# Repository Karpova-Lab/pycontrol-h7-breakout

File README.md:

> !!! WARNING !!! This is a work in progress. Please see the [discussion](https://github.com/orgs/pyControl/discussions/171) to see updates and provide feedback.
# pyControl H7 Breakout
A pyControl breakout board using an [STM32H743VIT6](https://www.digikey.com/short/7n8h83wr) microcontroller.

- 480 MHz Cortex-M7, 800 KB SRAM, 32 MB QSPI flash
- 10 pyControl RJ45 behavior ports
- 8 position [terminal block](https://www.digikey.com/short/fpqf2rj0) that pairs with a [screw terminal plug](https://www.digikey.com/short/n57m4m7h)
- 2 BNC connectors
- 1 [QWIIC](https://www.sparkfun.com/qwiic) / [Stemma-QT](https://learn.adafruit.com/introducing-adafruit-stemma-qt/what-is-stemma-qt) / [Modulino](https://store.arduino.cc/collections/modulino) connector
- USB type C connector with ESD protection
- On/off toggle switch, 4 user buttons, reset button, and a DFU button for bootloader access
- Power and USB indicator LEDs, 4 user controllable LEDs (red, yellow, green and blue)
- Metal enclosure 
- Mounting hole spacing compatible with [DIN adapters](https://www.digikey.com/short/h7977mfv) that securely mount onto [DIN rail](https://www.digikey.com/en/products/filter/hardware-fasteners-accessories/580?s=N4IgjCBcpgHAzFUBjKAzAhgGwM4FMAaEAeygG0QAWMeWSgThAF0iAHAFyhAGV2AnAJYA7AOYgAvkQC0AJiQhUkfgFdCJciACszcZJBzIFACIBJAHIACPhgFYQRU5eu2dQA)

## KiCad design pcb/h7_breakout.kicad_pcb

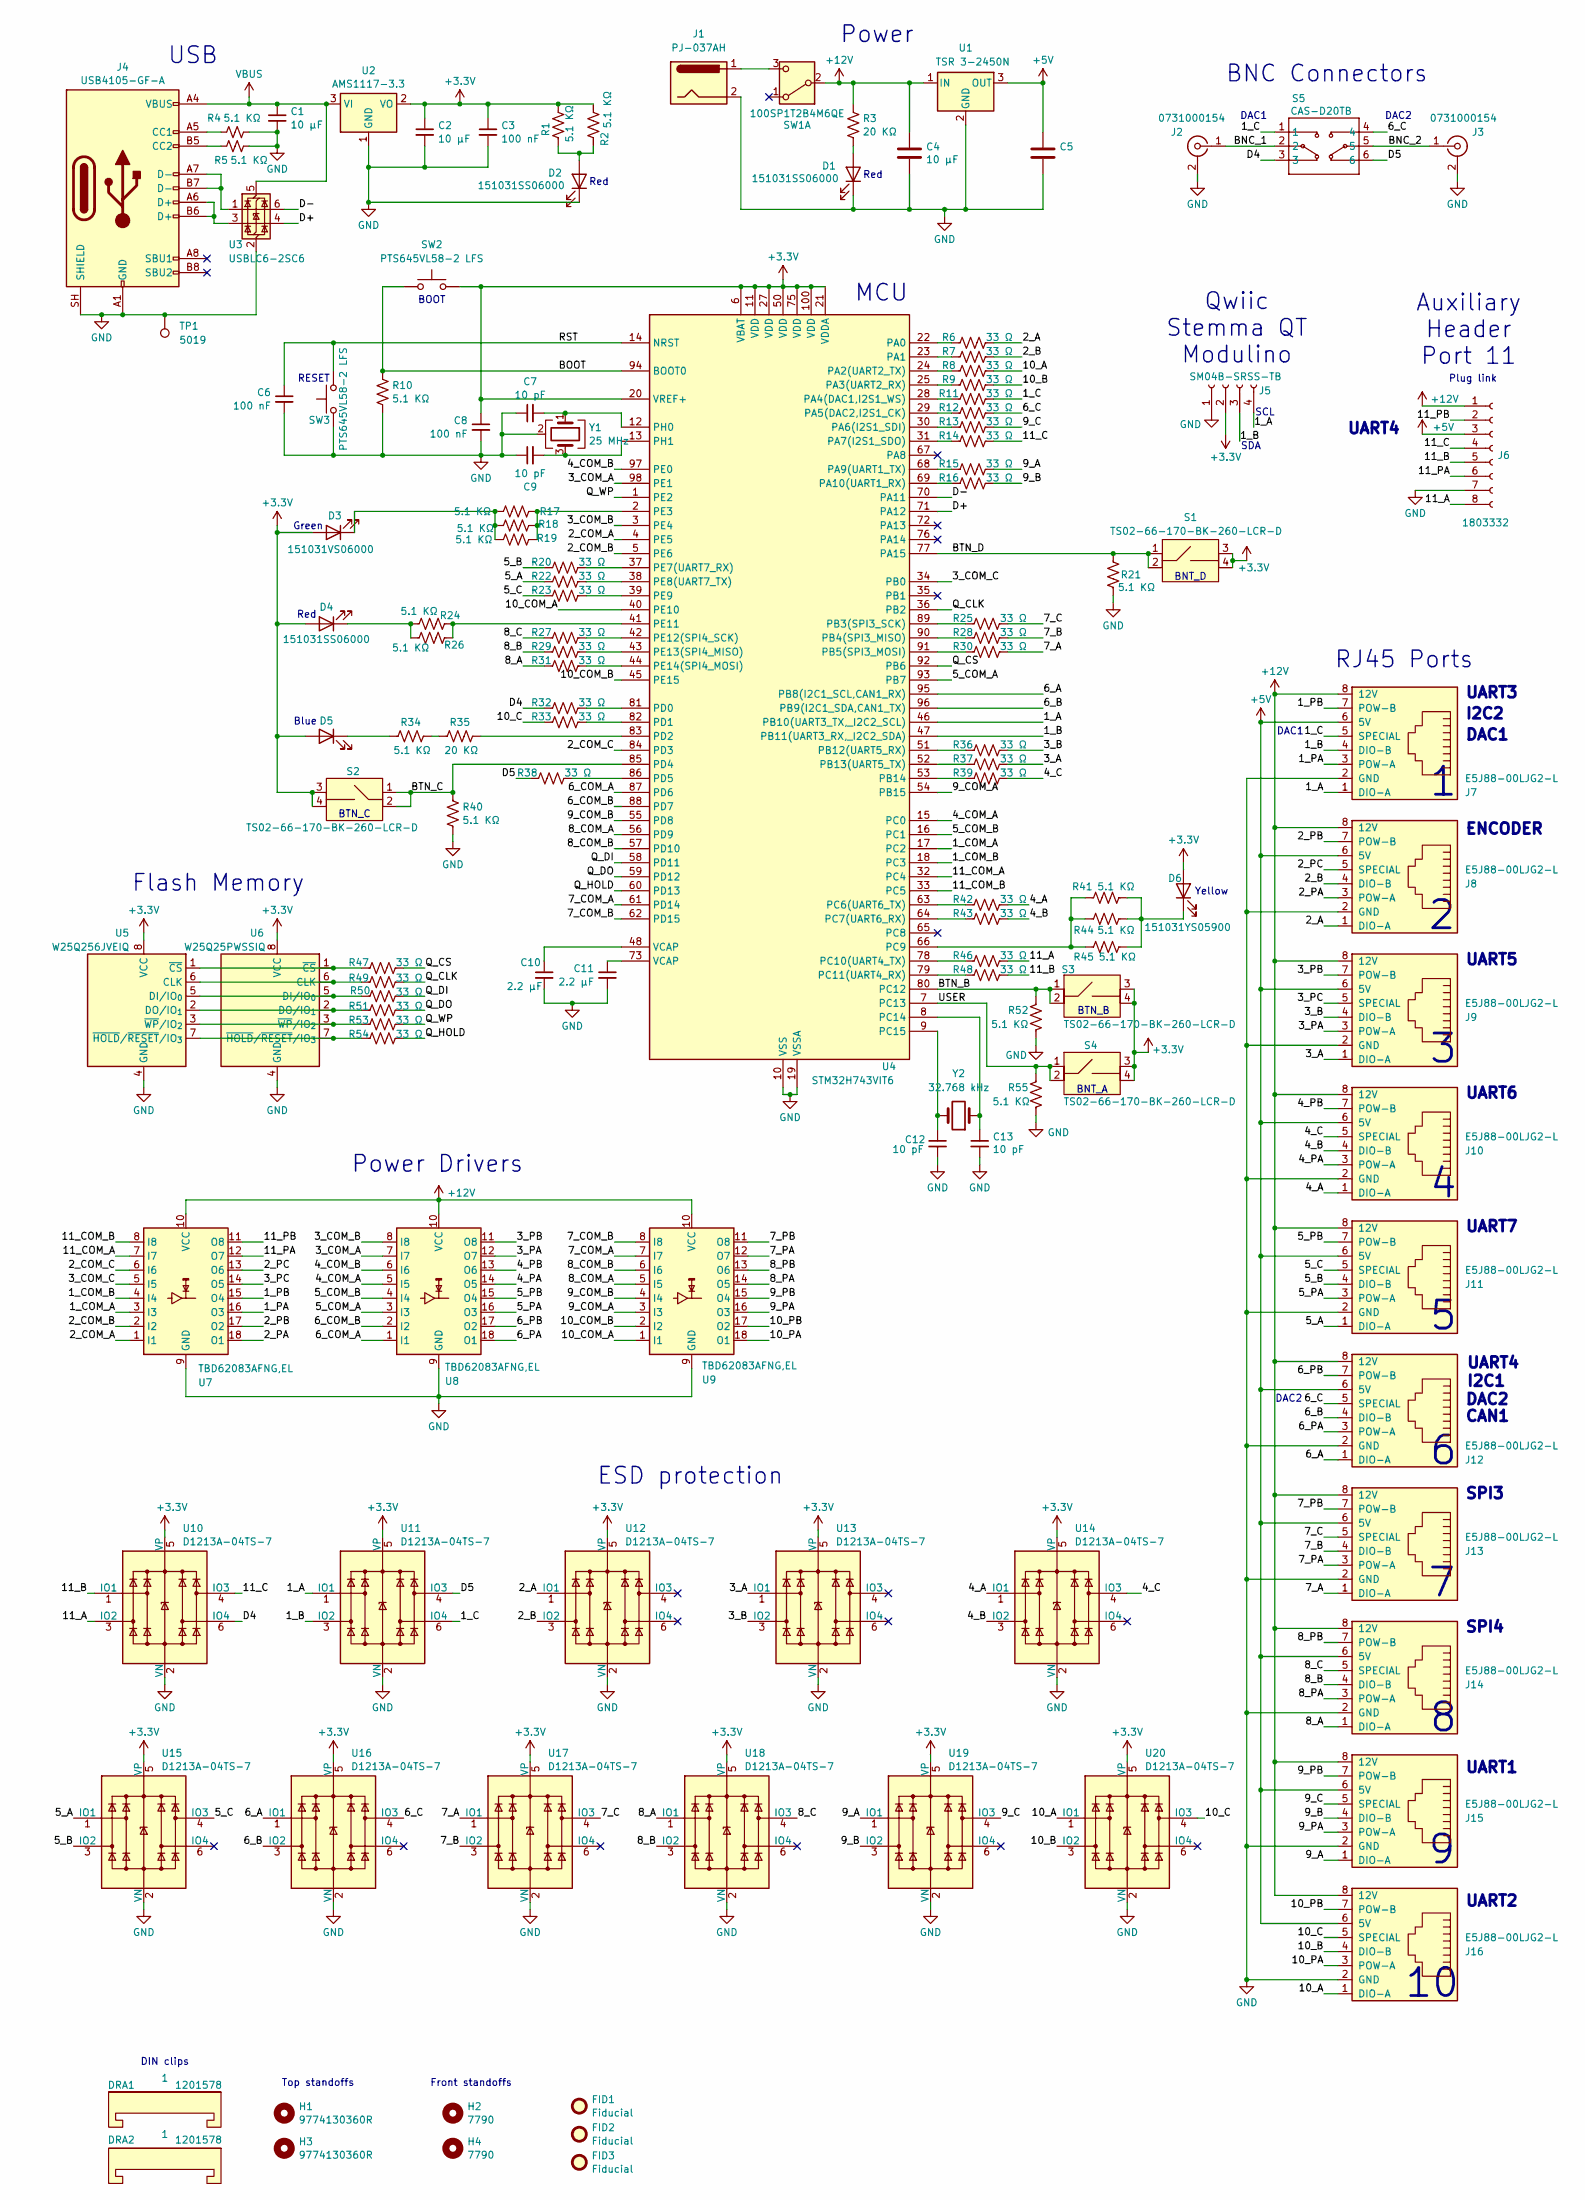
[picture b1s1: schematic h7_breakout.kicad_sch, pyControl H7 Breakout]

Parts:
C1, C2, C4, C5: 10 µF; C_1206_3216Metric_Pad1.33x1.80mm_HandSolder
C3, C6, C8: 100 nF; C_0603_1608Metric_Pad1.08x0.95mm_HandSolder
C7, C9, C12, C13: 10 pF; C_0603_1608Metric_Pad1.08x0.95mm_HandSolder
C10, C11: 2.2 µF; C_0603_1608Metric_Pad1.08x0.95mm_HandSolder
D1, D2, D4: 151031SS06000; LED_D3.0mm
D3: 151031VS06000; LED_D3.0mm
D5: 151033BS03000; LED_D3.0mm
D6: 151031YS05900; LED_D3.0mm
DRA1, DRA2: 1201578; DIN_Clip
FID1, FID2, FID3: Fiducial; Fiducial_0.75mm_Mask2.25mm
H1, H3: 9774130360R; standoff_nut
H2, H4: 7790; RA_screw_mount
J1: PJ-037AH; DC_Jack
J2, J3: 0731000154; BNC RA Jack
J4: USB4105-GF-A; USB_C_Receptacle_GCT_USB4105-xx-A_16P_TopMnt_Horizontal
J5: SM04B-SRSS-TB; JST_SH_SM04B-SRSS-TB_1x04-1MP_P1.00mm_Horizontal
J6: 1803332; PhoenixContact_MC_1,5_8-G-3.81_1x08_P3.81mm_Horizontal
J7, J8, J9, J10, J11, J12, J13, J14, J15, J16: E5J88-00LJG2-L; RJ45_THP_tab_on_top
R1, R2, R4, R5, R10, R17, R18, R19, R21, R24, R26, R34, R40, R41, R44, R45, R52, R55: 5.1 KΩ; R_0603_1608Metric_Pad0.98x0.95mm_HandSolder
R3, R35: 20 KΩ; R_0603_1608Metric_Pad0.98x0.95mm_HandSolder
R6, R7, R8, R9, R11, R12, R13, R14, R15, R16, R20, R22, R23, R25, R27, R28, R29, R30, R31, R32, R33, R36, R37, R38, R39, R42, R43, R46, R47, R48, R49, R50, R51, R53, R54: 33 Ω; R_0603_1608Metric_Pad0.98x0.95mm_HandSolder
S1, S2, S3, S4: TS02-66-170-BK-260-LCR-D; SW_TH_Tactile_TS02-66-170
S5: CAS-D20TB
SW1: 100SP1T2B4M6QE; RA toggle
SW2, SW3: PTS645VL58-2 LFS; SW_Tactile_SPST_Angled_PTS645Vx58-2LFS
TP1: 5019; TestPoint_Plated_Hole_D2.0mm
U1: TSR 3-2450N; Converter_DCDC_traco_3A
U2: AMS1117-3.3; SOT-223-3_TabPin2
U3: USBLC6-2SC6; SOT-23-6; LCSC C7519
U4: STM32H743VIT6; LQFP-100_14x14mm_P0.5mm; LCSC C114409
U5: W25Q256JVEIQ; WSON-8-1EP_8x6mm_P1.27mm_EP3.4x4.3mm; LCSC C97522
U6: W25Q25PWSSIQ; SOIC-8_5.3x5.3mm_P1.27mm
U7, U8, U9: TBD62083AFNG,EL; SSOP-18_4.4x6.5mm_P0.65mm; LCSC C163229
U10, U11, U12, U13, U14, U15, U16, U17, U18, U19, U20: D1213A-04TS-7; SOT-23-6; LCSC C460588
Y1: 25 MHz; crystal_STDCRS2-25M
Y2: 32.768 kHz; Crystal_SMD_EuroQuartz_EQ161-2Pin_3.2x1.5mm_HandSoldering

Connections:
+5V: C5.1, J6.3, J7.6 (5V), J8.6 (5V), J9.6 (5V), J10.6 (5V), J11.6 (5V), J12.6 (5V), J13.6 (5V), J14.6 (5V), J15.6 (5V), J16.6 (5V), U1.3 (OUT)
+12V: C4.1, J6.1, J7.8 (12V), J8.8 (12V), J9.8 (12V), J10.8 (12V), J11.8 (12V), J12.8 (12V), J13.8 (12V), J14.8 (12V), J15.8 (12V), J16.8 (12V), R3.1, SW1.2 (B), U1.1 (IN), U7.10 (VCC), U8.10 (VCC), U9.10 (VCC)
/1_A: J5.4, J7.1 (DIO-A), U4.46 (PB10(UART3_TX,_I2C2_SCL)), U11.1 (IO1)
/1_B: J5.3, J7.4 (DIO-B), U4.47 (PB11(UART3_RX,_I2C2_SDA)), U11.3 (IO2)
/1_C: J7.5 (SPECIAL), R11.2, S5.1, U11.6 (IO4)
/1_COM_A: U4.17 (PC2), U7.3 (I3)
/1_COM_B: U4.18 (PC3), U7.4 (I4)
/1_PA: J7.3 (POW-A), U7.16 (O3)
/1_PB: J7.7 (POW-B), U7.15 (O4)
/2_A: J8.1 (DIO-A), R6.2, U12.1 (IO1)
/2_B: J8.4 (DIO-B), R7.2, U12.3 (IO2)
/2_COM_A: U4.4 (PE5), U7.1 (I1)
/2_COM_B: U4.5 (PE6), U7.2 (I2)
/2_COM_C: U4.84 (PD3), U7.6 (I6)
/2_PA: J8.3 (POW-A), U7.18 (O1)
/2_PB: J8.7 (POW-B), U7.17 (O2)
/2_PC: J8.5 (SPECIAL), U7.13 (O6)
/3_A: J9.1 (DIO-A), R37.2, U13.1 (IO1)
/3_B: J9.4 (DIO-B), R36.2, U13.3 (IO2)
/3_COM_A: U4.98 (PE1), U8.7 (I7)
/3_COM_B: U4.3 (PE4), U8.8 (I8)
/3_COM_C: U4.34 (PB0), U7.5 (I5)
/3_PA: J9.3 (POW-A), U8.12 (O7)
/3_PB: J9.7 (POW-B), U8.11 (O8)
/3_PC: J9.5 (SPECIAL), U7.14 (O5)
/4_A: J10.1 (DIO-A), R42.2, U14.1 (IO1)
/4_B: J10.4 (DIO-B), R43.2, U14.3 (IO2)
/4_C: J10.5 (SPECIAL), R39.2, U14.4 (IO3)
/4_COM_A: U4.15 (PC0), U8.5 (I5)
/4_COM_B: U4.97 (PE0), U8.6 (I6)
/4_PA: J10.3 (POW-A), U8.14 (O5)
/4_PB: J10.7 (POW-B), U8.13 (O6)
/5_A: J11.1 (DIO-A), R22.1, U15.1 (IO1)
/5_B: J11.4 (DIO-B), R20.1, U15.3 (IO2)
/5_C: J11.5 (SPECIAL), R23.1, U15.4 (IO3)
/5_COM_A: U4.93 (PB7), U8.3 (I3)
/5_COM_B: U4.16 (PC1), U8.4 (I4)
/5_PA: J11.3 (POW-A), U8.16 (O3)
/5_PB: J11.7 (POW-B), U8.15 (O4)
/6_A: J12.1 (DIO-A), U4.95 (PB8(I2C1_SCL,CAN1_RX)), U16.1 (IO1)
/6_B: J12.4 (DIO-B), U4.96 (PB9(I2C1_SDA,CAN1_TX)), U16.3 (IO2)
/6_C: J12.5 (SPECIAL), R12.2, S5.4, U16.4 (IO3)
/6_COM_A: U4.87 (PD6), U8.1 (I1)
/6_COM_B: U4.88 (PD7), U8.2 (I2)
/6_PA: J12.3 (POW-A), U8.18 (O1)
/6_PB: J12.7 (POW-B), U8.17 (O2)
/7_A: J13.1 (DIO-A), R30.2, U17.1 (IO1)
/7_B: J13.4 (DIO-B), R28.2, U17.3 (IO2)
/7_C: J13.5 (SPECIAL), R25.2, U17.4 (IO3)
/7_COM_A: U4.61 (PD14), U9.7 (I7)
/7_COM_B: U4.62 (PD15), U9.8 (I8)
/7_PA: J13.3 (POW-A), U9.12 (O7)
/7_PB: J13.7 (POW-B), U9.11 (O8)
/8_A: J14.1 (DIO-A), R31.1, U18.1 (IO1)
/8_B: J14.4 (DIO-B), R29.1, U18.3 (IO2)
/8_C: J14.5 (SPECIAL), R27.1, U18.4 (IO3)
/8_COM_A: U4.56 (PD9), U9.5 (I5)
/8_COM_B: U4.57 (PD10), U9.6 (I6)
/8_PA: J14.3 (POW-A), U9.14 (O5)
/8_PB: J14.7 (POW-B), U9.13 (O6)
/9_A: J15.1 (DIO-A), R15.2, U19.1 (IO1)
/9_B: J15.4 (DIO-B), R16.2, U19.3 (IO2)
/9_C: J15.5 (SPECIAL), R13.2, U19.4 (IO3)
/9_COM_A: U4.54 (PB15), U9.3 (I3)
/9_COM_B: U4.55 (PD8), U9.4 (I4)
/9_PA: J15.3 (POW-A), U9.16 (O3)
/9_PB: J15.7 (POW-B), U9.15 (O4)
/10_A: J16.1 (DIO-A), R8.2, U20.1 (IO1)
/10_B: J16.4 (DIO-B), R9.2, U20.3 (IO2)
/10_C: J16.5 (SPECIAL), R33.1, U20.4 (IO3)
/10_COM_A: U4.40 (PE10), U9.1 (I1)
/10_COM_B: U4.45 (PE15), U9.2 (I2)
/10_PA: J16.3 (POW-A), U9.18 (O1)
/10_PB: J16.7 (POW-B), U9.17 (O2)
/11_A: J6.8, R46.2, U10.3 (IO2)
/11_B: J6.5, R48.2, U10.1 (IO1)
/11_C: J6.4, R14.2, U10.4 (IO3)
/11_COM_A: U4.32 (PC4), U7.7 (I7)
/11_COM_B: U4.33 (PC5), U7.8 (I8)
/11_PA: J6.6, U7.12 (O7)
/11_PB: J6.2, U7.11 (O8)
/BNC_1: J2.1 (In), S5.2
/BNC_2: J3.1 (In), S5.5
/BTN_B: R52.2, S3.1 (in1), S3.2 (in2), U4.80 (PC12)
/BTN_C: R40.2, S2.1 (in1), S2.2 (in2), U4.85 (PD4)
/BTN_D: R21.2, S1.1 (in1), S1.2 (in2), U4.77 (PA15)
/D4: R32.1, S5.3, U10.6 (IO4)
/D5: R38.1, S5.6, U11.4 (IO3)
/D+: U3.4 (I/O2), U4.71 (PA12)
/D-: U3.6 (I/O1), U4.70 (PA11)
/Q_CLK: R49.2, U4.36 (PB2)
/Q_CS: R47.2, U4.92 (PB6)
/Q_DI: R50.2, U4.58 (PD11)
/Q_DO: R51.2, U4.59 (PD12)
/Q_HOLD: R54.2, U4.60 (PD13)
/Q_WP: R53.2, U4.1 (PE2)
/USER: R55.2, S4.1 (in1), S4.2 (in2), U4.7 (PC13)
unnamed: C10.1, U4.48 (VCAP)
unnamed: C11.1, U4.73 (VCAP)
unnamed: D1.2 (A), R3.2
unnamed: D2.2 (A), R1.2, R2.2
unnamed: D3.1 (K), R17.1, R18.1, R19.1
unnamed: D4.1 (K), R24.1, R26.1
unnamed: D5.1 (K), R34.1
unnamed: D6.1 (K), R41.2, R44.2, R45.2
unnamed: J4.A5 (CC1), R4.1
unnamed: J4.B5 (CC2), R5.2
unnamed: J4.A6 (D+), J4.B6 (D+), U3.3 (I/O2)
unnamed: J4.A7 (D-), J4.B7 (D-), U3.1 (I/O1)
unnamed: R34.2, R35.1
unnamed: J1.1, SW1.3 (C)
unnamed: R6.1, U4.22 (PA0)
unnamed: R7.1, U4.23 (PA1)
unnamed: R8.1, U4.24 (PA2(UART2_TX))
unnamed: R9.1, U4.25 (PA3(UART2_RX))
unnamed: R11.1, U4.28 (PA4(DAC1,I2S1_WS))
unnamed: R12.1, U4.29 (PA5(DAC2,I2S1_CK))
unnamed: R13.1, U4.30 (PA6(I2S1_SDI))
unnamed: R14.1, U4.31 (PA7(I2S1_SDO))
unnamed: R15.1, U4.68 (PA9(UART1_TX))
unnamed: R16.1, U4.69 (PA10(UART1_RX))
unnamed: R25.1, U4.89 (PB3(SPI3_SCK))
unnamed: R28.1, U4.90 (PB4(SPI3_MISO))
unnamed: R30.1, U4.91 (PB5(SPI3_MOSI))
unnamed: R36.1, U4.51 (PB12(UART5_RX))
unnamed: R37.1, U4.52 (PB13(UART5_TX))
unnamed: R39.1, U4.53 (PB14)
unnamed: R42.1, U4.63 (PC6(UART6_TX))
unnamed: R43.1, U4.64 (PC7(UART6_RX))
unnamed: R41.1, R44.1, R45.1, U4.66 (PC9)
unnamed: R46.1, U4.78 (PC10(UART4_TX))
unnamed: R48.1, U4.79 (PC11(UART4_RX))
unnamed: C13.1, U4.8 (PC14), Y2.1
unnamed: C12.1, U4.9 (PC15), Y2.2
unnamed: R32.2, U4.81 (PD0)
unnamed: R33.2, U4.82 (PD1)
unnamed: R35.2, U4.83 (PD2)
unnamed: R38.2, U4.86 (PD5)
unnamed: R17.2, R18.2, R19.2, U4.2 (PE3)
unnamed: R20.2, U4.37 (PE7(UART7_RX))
unnamed: R22.2, U4.38 (PE8(UART7_TX))
unnamed: R23.2, U4.39 (PE9)
unnamed: R24.2, R26.2, U4.41 (PE11)
unnamed: R27.2, U4.42 (PE12(SPI4_SCK))
unnamed: R29.2, U4.43 (PE13(SPI4_MISO))
unnamed: R31.2, U4.44 (PE14(SPI4_MOSI))
unnamed: C7.2, U4.12 (PH0), Y1.1
unnamed: C9.2, U4.13 (PH1), Y1.3
unnamed: R49.1, U5.6 (CLK), U6.6 (CLK)
unnamed: R50.1, U5.5 (DI/IO_{0}), U6.5 (DI/IO_{0})
unnamed: R51.1, U5.2 (DO/IO_{1}), U6.2 (DO/IO_{1})
unnamed: R47.1, U5.1 (~CS), U6.1 (~CS)
unnamed: R54.1, U5.7 (~HOLD/~RESET/IO_{3}), U6.7 (~HOLD/~RESET/IO_{3})
unnamed: R53.1, U5.3 (~WP/IO_{2}), U6.3 (~WP/IO_{2})
VBUS: C1.1, J4.A4 (VBUS), J4.A9 (VBUS), J4.B4 (VBUS), J4.B9 (VBUS), U2.3 (VI), U3.5 (VBUS)

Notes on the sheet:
SDA
DAC2
I2C2
UART4
Plug link
Power Drivers
Auxiliary Header Port 11
ESD protection
DIN clips
ENCODER
BOOT
USB
Red
SPI4
Qwiic Stemma QT Modulino
I2C1
BTN_B
RJ45 Ports
BNT_D
SCL
Flash Memory
BNT_A
DAC1
UART6
SPI3
UART1
UART3
Blue
UART7
UART2
RESET
Green
Front standoffs
BNC Connectors
UART5
Power
Yellow
CAN1
BTN_C
MCU

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
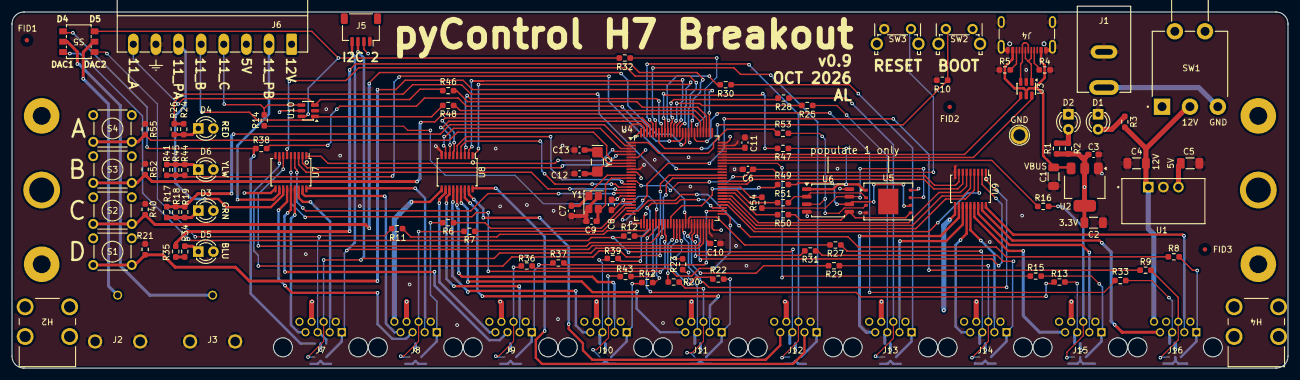
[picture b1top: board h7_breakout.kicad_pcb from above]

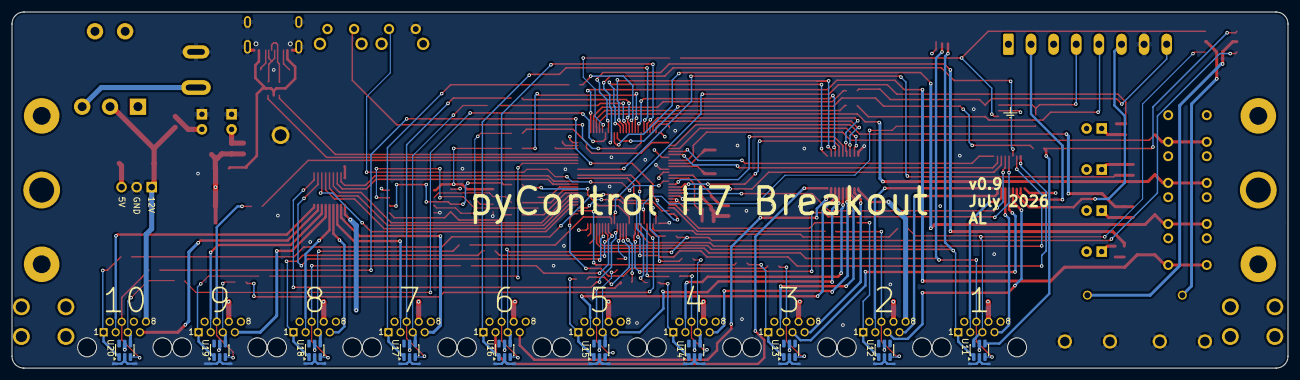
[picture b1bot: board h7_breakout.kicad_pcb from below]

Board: 4 copper layers, 215.0 x 60.0 mm, 130 parts (12 on the bottom side), 159 nets.

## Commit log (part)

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2026-02-25 v0.1
2026-03-12 PCB v0.2
2026-03-25 add Janelia licenses
2026-03-26 PCB v0.3
    don't short the power supply with the on/off switch 🤦
    flipped UART4 pins. TX(4_A)/RX(4_B) was PC11(79)/PC10(78), now PC10(78)/PC11(79)
    connect Vref to 3.3V so DAC works
    change RGB LEDs to 10k
2026-03-26 add readme
2026-03-26 readme update
2026-04-16 PCB v0.4
    - was 2 layer, now 4 layer board
    - was USB type B, now USB type C connector
    - was SMA coaxial connectors, now BNC
    - was 12 ports, now 10 ports
    - added POW_C pins to 2 of the ports
    - added8 extra GPIOs, 2 POW pins, and 5V/12V/GND rails on 16 pin terminal block
2026-05-16 PCB v0.5
    - connect USB-C shield ground
    - connect A6/B6 and A7/B7 on USB-C
    - connect C13 to ground
    - use 5.1K resistors for everything
    - make DC-DC converter pads smaller
    - added QR code
2026-06-08 PCB v0.6
